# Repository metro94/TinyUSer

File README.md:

# TinyUSer - USB to Serial powered by CH340X

## Introduction

A tiny USB-to-Serial baord in just ~10x18 mm^2, powered by CH340X with *DTR#* supported.

## 3D Rendering View

## License

[CERN-OHL-P](LICENSE)

## EDA

KiCad 6.0.6

## Usages

This PCB can be used with both CH340E and CH340X. For CH340X, *TNOW* can be replaced by *DTR#*, which is useful for UART download purpose.

If 5V IO voltage level is desired, *5V* to *VCC* shall be shorten by 0Ω resistor, and *R3* shall **NOT** be connected. LDO is not required and can be left unconnected.

If 3.3V IO voltage level is desired, *3V3* to *VCC* shall be shorten by 0Ω resistor, and *R3* shall be connected. LDO is required and two 1μF capacitors should be connected.

If *DTR#* is desired, *DTR* shall be connected to *OS* (Open-Source) or *PP* (Push-Pull) by 4.7kΩ resistor, otherwise left unconnected.

### Schematics

[TinyUSer Schematic](schematics/TinyUSer.pdf)

### BOM

[TinyUSer BOM](https://metro94.github.io/TinyUSer/bom.html)

### Product Page

[USB to Serial Port Chip CH340 - NanjingQinhengMicroelectronics](http://www.wch-ic.com/products/CH340.html)

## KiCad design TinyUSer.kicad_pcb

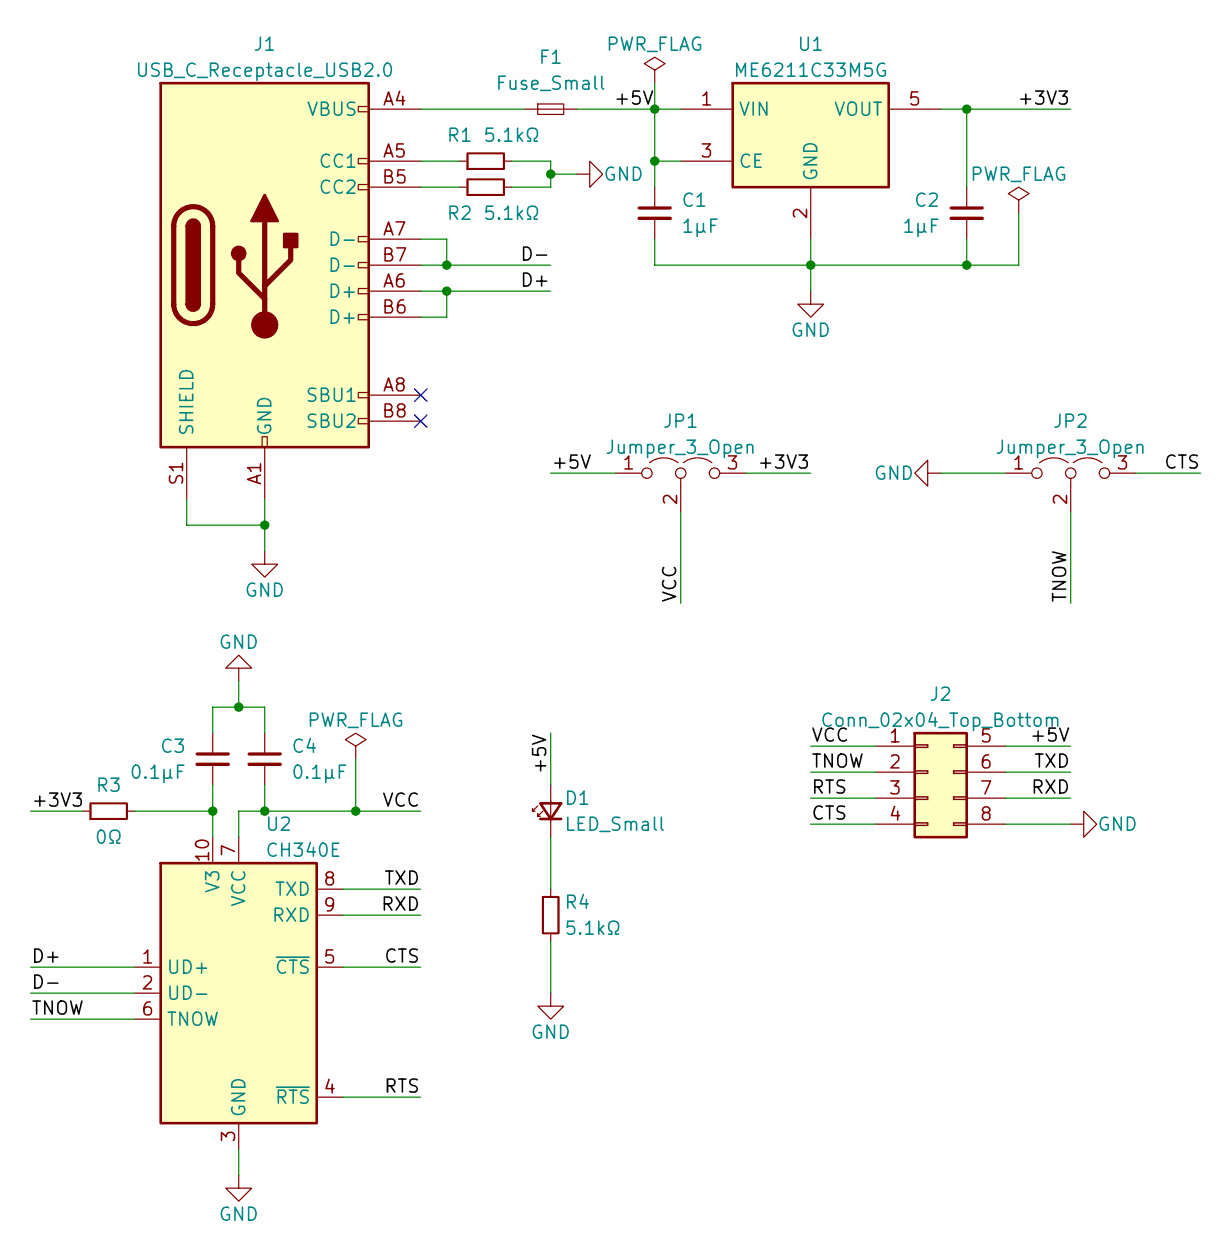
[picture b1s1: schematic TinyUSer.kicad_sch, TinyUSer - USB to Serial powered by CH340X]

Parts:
C1, C2: 1μF; C_0603_1608Metric
C3, C4: 0.1μF; C_0603_1608Metric
D1: LED_Small; LED_0603_1608Metric
F1: Fuse_Small; Fuse_0603_1608Metric
J1: USB_C_Receptacle_USB2.0; USB_C_Receptacle_Palconn_UTC16-G
J2: Conn_02x04_Top_Bottom; Pin_2x04_P2.54mm_NoSilkscreen
JP1, JP2: Jumper_3_Open; Jumper-3
R1, R2, R4: 5.1kΩ; R_0603_1608Metric
R3: 0Ω; R_0603_1608Metric
U1: ME6211C33M5G; SOT-23-5
U2: CH340E; MSOP-10_3x3mm_P0.5mm

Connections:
/+3V3: C2.1, JP1.3 (B), R3.1, U1.5 (VOUT)
/+5V: C1.1, D1.2 (A), F1.2, J2.5, JP1.1 (A), U1.1 (VIN), U1.3 (CE)
/CTS: J2.4, JP2.3 (B), U2.5 (~CTS)
/D+: J1.A6 (D+), J1.B6 (D+), U2.1 (UD+)
/D-: J1.A7 (D-), J1.B7 (D-), U2.2 (UD-)
/RTS: J2.3, U2.4 (~RTS)
/RXD: J2.7, U2.9 (RXD)
/TNOW: J2.2, JP2.2 (C), U2.6 (TNOW)
/TXD: J2.6, U2.8 (TXD)
/VCC: C4.2, J2.1, JP1.2 (C), U2.7 (VCC)
GND: C1.2, C2.2, C3.1, C4.1, J1.A1 (GND), J1.A12 (GND), J1.B1 (GND), J1.B12 (GND), J1.S1 (SHIELD), J2.8, JP2.1 (A), R1.2, R2.2, R4.2, U1.2 (GND), U2.3 (GND)
unnamed: C3.2, R3.2, U2.10 (V3)
unnamed: D1.1 (K), R4.1
unnamed: F1.1, J1.A4 (VBUS), J1.A9 (VBUS), J1.B4 (VBUS), J1.B9 (VBUS)
unnamed: J1.A5 (CC1), R1.1
unnamed: J1.B5 (CC2), R2.1

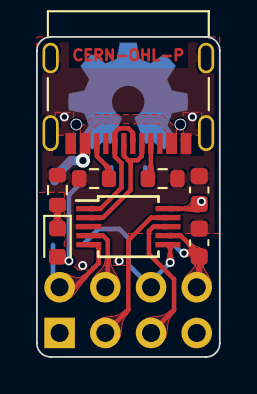
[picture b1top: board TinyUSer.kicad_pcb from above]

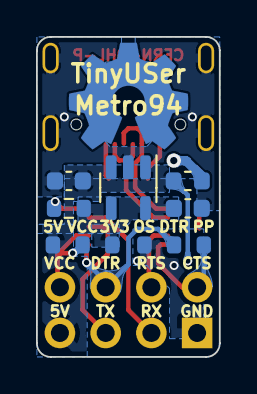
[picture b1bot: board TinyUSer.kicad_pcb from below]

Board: 2 copper layers, 10.2 x 17.8 mm, 16 parts (7 on the bottom side), 16 nets.

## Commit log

2022-11-01 Rev A.1 released
